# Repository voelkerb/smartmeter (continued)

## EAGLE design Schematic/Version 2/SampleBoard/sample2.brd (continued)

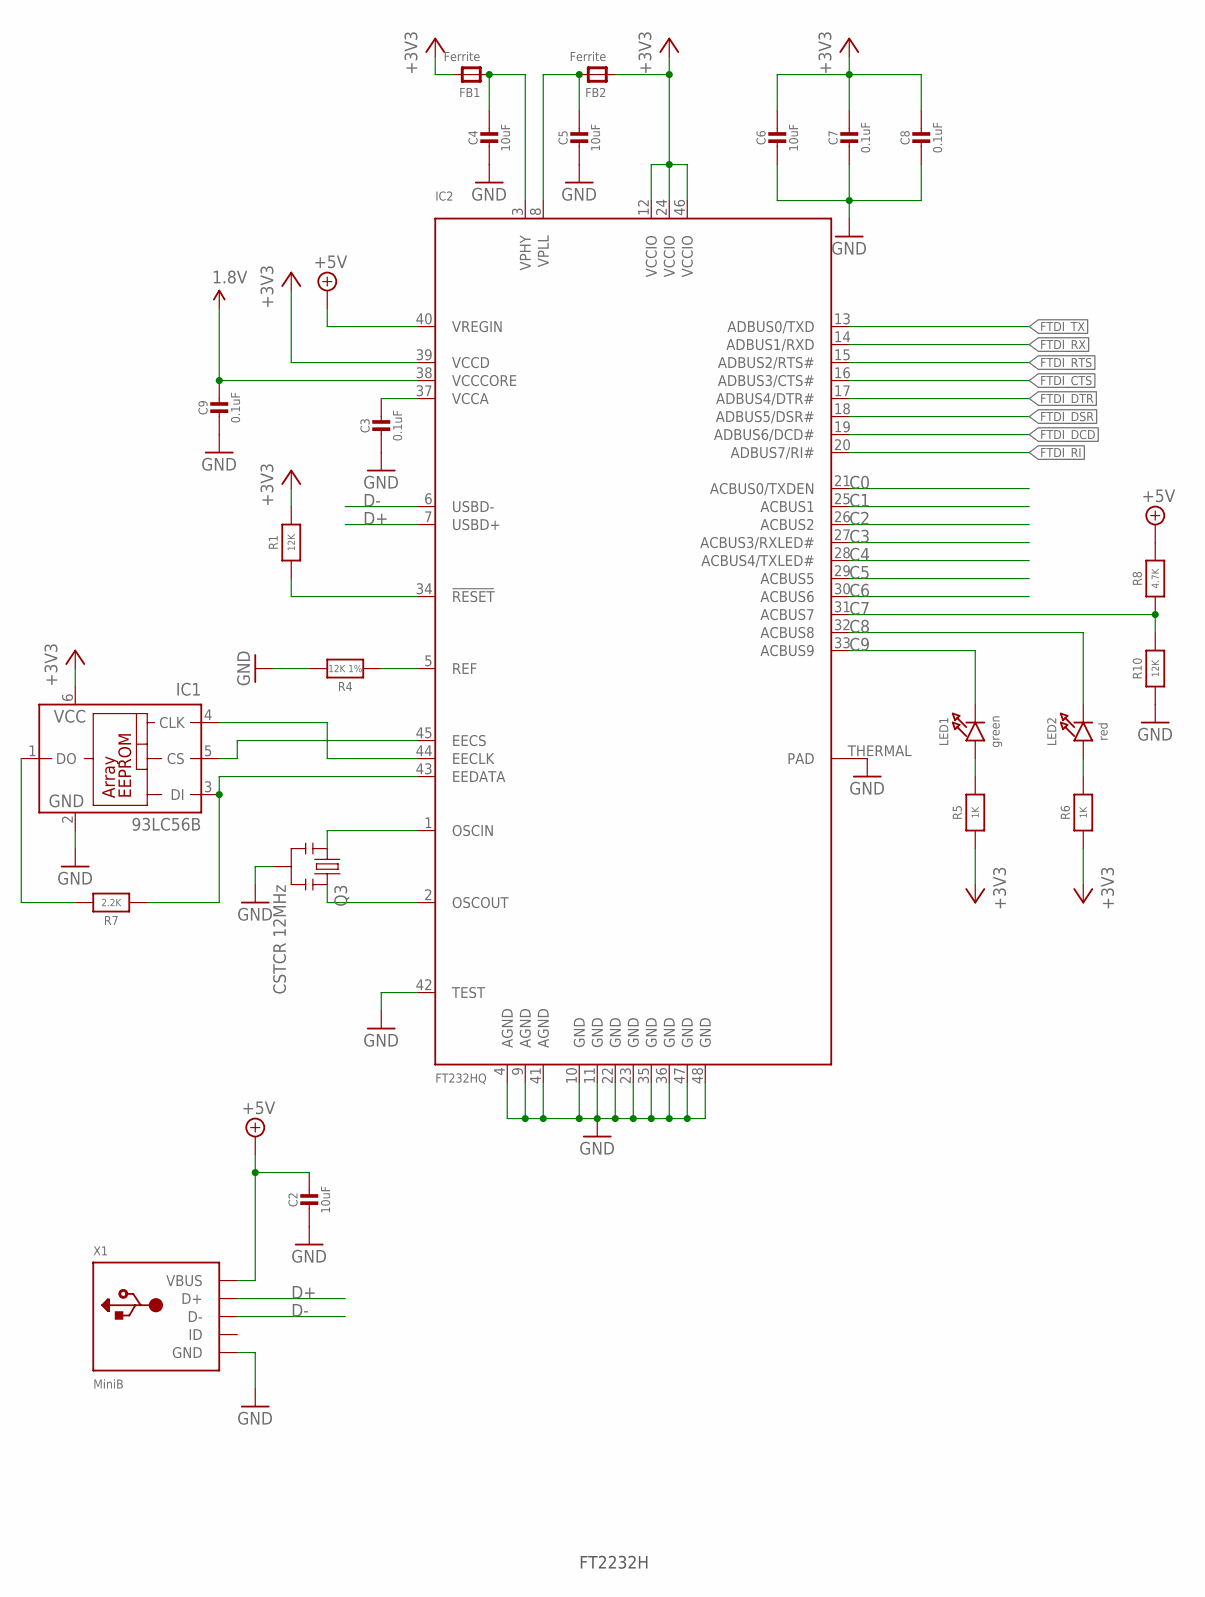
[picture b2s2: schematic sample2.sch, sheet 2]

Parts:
C2, C4, C5, C6: 10uF; _0603MP
C3, C7, C8, C9: 0.1uF; _0603MP
FB1: Ferrite; _0603
FB2: Ferrite; _0603MP
IC1: 93LC56B; SOT23-6
IC2: FT232HQ; QFN48_8MM
LED1: green; CHIPLED_0603_NOOUTLINE
LED2: red; CHIPLED_0603_NOOUTLINE
Q3: CSTCR 12MHz; RESONATOR-SMD
R1, R10: 12K; _0603MP
R4: 12K 1%; _0603MP
R5, R6: 1K; _0603MP
R7: 2.2K; _0603MP
R8: 4.7K; _0603MP
X1: MiniB; 4UCONN_20329

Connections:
1.8V: C9.1, IC2.38 (VCCCORE)
+3V3: C6.1, C7.1, C8.1, FB1.2, FB2.1, IC1.6 (VCC), IC2.12 (VCCIO), IC2.24 (VCCIO), IC2.39 (VCCD), IC2.46 (VCCIO), R1.2, R5.1, R6.1; also elsewhere on the board
+5V: C2.1, IC2.40 (VREGIN), R8.2, X1.VBUS
C0: IC2.21 (ACBUS0/TXDEN)
C1: IC2.25 (ACBUS1)
C2: IC2.26 (ACBUS2)
C3: IC2.27 (ACBUS3/RXLED#)
C4: IC2.28 (ACBUS4/TXLED#)
C5: IC2.29 (ACBUS5)
C6: IC2.30 (ACBUS6)
C7: IC2.31 (ACBUS7), R8.1, R10.2
C8: IC2.32 (ACBUS8), LED2.C
C9: IC2.33 (ACBUS9), LED1.C
D+: IC2.7 (USBD+), X1.D+
D-: IC2.6 (USBD-), X1.D-
FTDI_CTS: IC2.16 (ADBUS3/CTS#)
FTDI_DCD: IC2.19 (ADBUS6/DCD#)
FTDI_DSR: IC2.18 (ADBUS5/DSR#)
FTDI_DTR: IC2.17 (ADBUS4/DTR#); also elsewhere on the board
FTDI_RI: IC2.20 (ADBUS7/RI#)
FTDI_RTS: IC2.15 (ADBUS2/RTS#); also elsewhere on the board
FTDI_RX: IC2.14 (ADBUS1/RXD); also elsewhere on the board
FTDI_TX: IC2.13 (ADBUS0/TXD); also elsewhere on the board
GND: C2.2, C3.2, C4.2, C5.2, C6.2, C7.2, C8.2, C9.2, IC1.2 (GND), IC2.4 (AGND), IC2.9 (AGND), IC2.10 (GND), IC2.11 (GND), IC2.22 (GND), IC2.23 (GND), IC2.35 (GND), IC2.36 (GND), IC2.41 (AGND), IC2.42 (TEST), IC2.47 (GND), IC2.48 (GND), IC2.THERMAL (PAD), Q3.2, R4.2, R10.1, X1.BASE@1 (GND), X1.BASE@2 (GND), X1.GND, X1.SPRT@1 (GND), X1.SPRT@2 (GND), X1.SPRT@3 (GND), X1.SPRT@4 (GND); also elsewhere on the board
unnamed: IC2.1 (OSCIN), Q3.1
unnamed: IC2.2 (OSCOUT), Q3.3
unnamed: IC2.5 (REF), R4.1
unnamed: LED2.A, R6.2
unnamed: IC2.34 (!RESET), R1.1
unnamed: LED1.A, R5.2
unnamed: IC1.3 (DI), IC2.43 (EEDATA), R7.1
unnamed: IC1.5 (CS), IC2.45 (EECS)
unnamed: IC1.4 (CLK), IC2.44 (EECLK)
unnamed: IC1.1 (DO), R7.2
VCCA: C3.1, IC2.37 (VCCA)
VPHY: C4.1, FB1.1, IC2.3 (VPHY)
VPLL: C5.1, FB2.2, IC2.8 (VPLL)

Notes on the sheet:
FT2232H

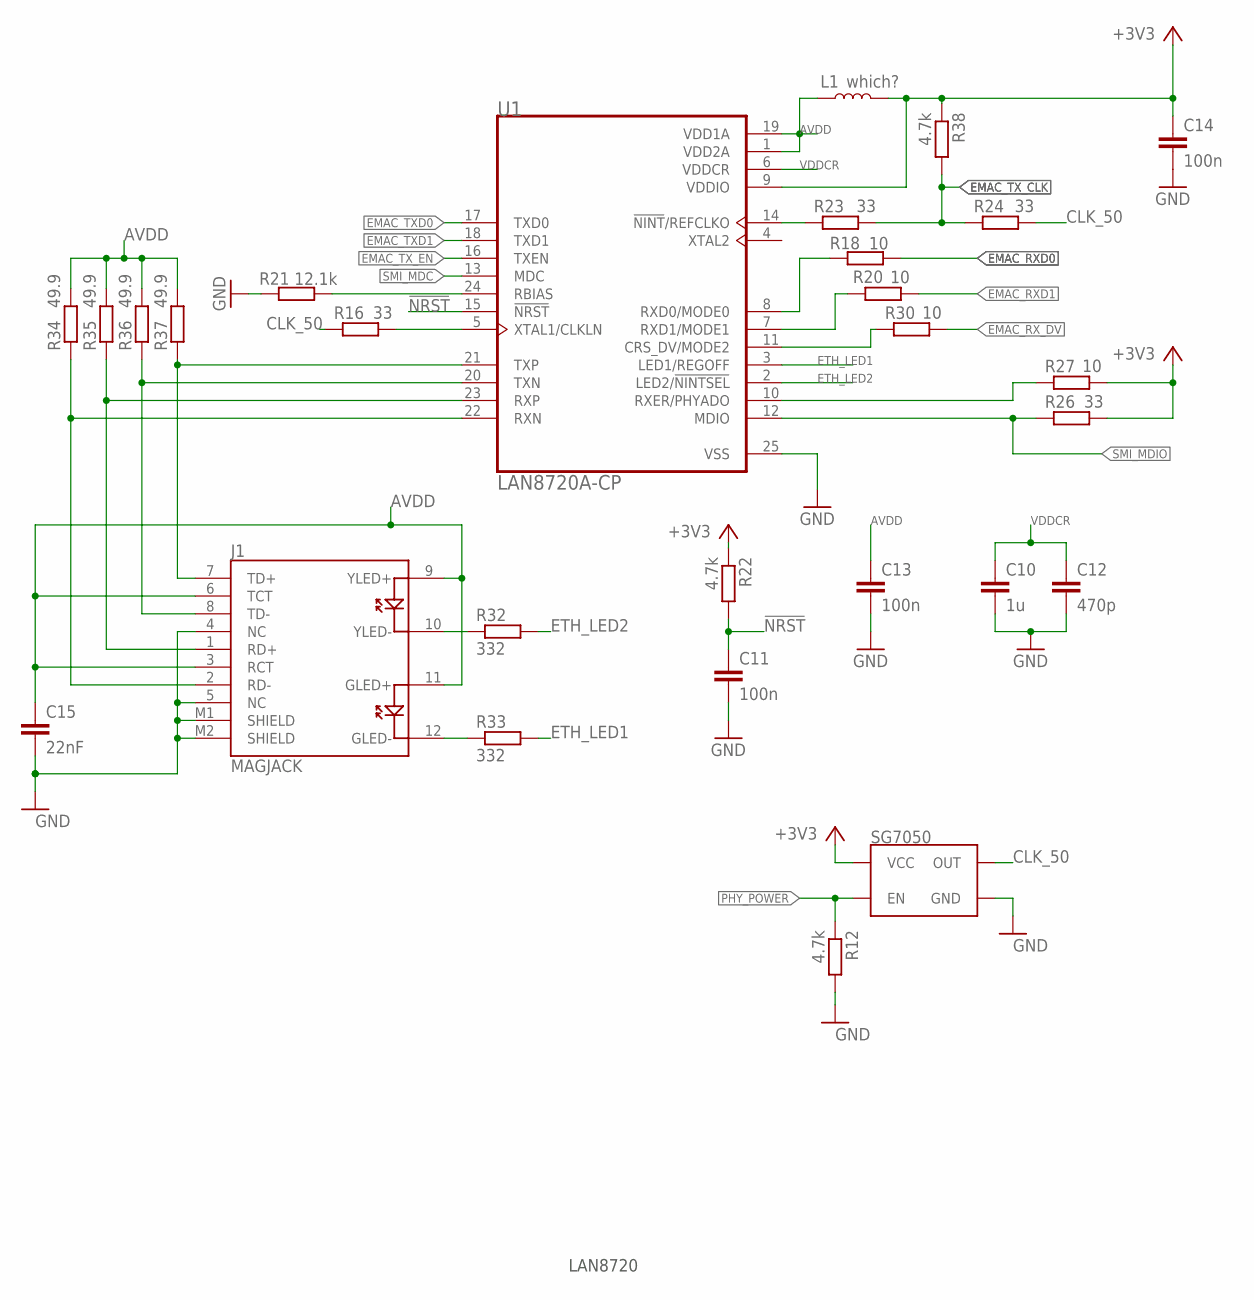
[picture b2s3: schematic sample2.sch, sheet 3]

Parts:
C10: 1u; C0402
C11, C13, C14: 100n; C0402
C12: 470p; C0402
C15: 22nF; C0402
J1: MAGJACK
L1: which?; 0603
R12, R22, R38: 4.7k; R0603
R16, R23, R24, R26: 33; R0603
R18, R20, R27, R30: 10; R0603
R21: 12.1k; R0603
R32, R33: 332; R0603
R34, R35, R36, R37: 49.9; R0603
SG7050: OSCILLATORSMD-7X5-4PAD; OSCILLATOR-SMD-7X5-4PAD
U1: LAN8720A-CP; QFN50P400X400X100-25N

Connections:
!NRST: C11.1, R22.2, U1.15 (!NRST)
+3V3: C14.1, L1.2, R22.1, R26.2, R27.2, R38.1, SG7050.4 (VCC), U1.9 (VDDIO); also elsewhere on the board
AVDD: C13.1, C15.1, J1.3 (RCT), J1.6 (TCT), J1.9 (YLED+), J1.11 (GLED+), L1.1, R34.2, R35.2, R36.2, R37.2, U1.1 (VDD2A), U1.19 (VDD1A)
CLK_50: R16.1, R24.2, SG7050.3 (OUT)
EMAC_RXD0: R18.1; also elsewhere on the board
EMAC_RXD1: R20.1; also elsewhere on the board
EMAC_RX_DV: R30.2; also elsewhere on the board
EMAC_TXD0: U1.17 (TXD0); also elsewhere on the board
EMAC_TXD1: U1.18 (TXD1); also elsewhere on the board
EMAC_TX_CLK: R23.2, R24.1, R38.2; also elsewhere on the board
EMAC_TX_EN: U1.16 (TXEN); also elsewhere on the board
ETH_LED1: R33.2, U1.3 (LED1/REGOFF)
ETH_LED2: R32.2, U1.2 (LED2/!NINTSEL!)
GND: C10.2, C11.2, C12.2, C13.2, C14.2, C15.2, J1.4 (NC), J1.5 (NC), J1.M1 (SHIELD), J1.M2 (SHIELD), R12.2, R21.2, SG7050.2 (GND), U1.25 (VSS); also elsewhere on the board
unnamed: R20.2, U1.7 (RXD1/MODE1)
unnamed: R18.2, U1.8 (RXD0/MODE0)
unnamed: R21.1, U1.24 (RBIAS)
unnamed: J1.10 (YLED-), R32.1
unnamed: R16.2, U1.5 (XTAL1/CLKLN)
unnamed: R27.1, U1.10 (RXER/PHYADO)
unnamed: R23.1, U1.14 (!NINT!/REFCLKO)
unnamed: R30.1, U1.11 (CRS_DV/MODE2)
unnamed: J1.12 (GLED-), R33.1
unnamed: J1.7 (TD+), R37.1, U1.21 (TXP)
unnamed: J1.8 (TD-), R36.1, U1.20 (TXN)
unnamed: J1.1 (RD+), R35.1, U1.23 (RXP)
unnamed: J1.2 (RD-), R34.1, U1.22 (RXN)
PHY_POWER: R12.1, SG7050.1 (EN); also elsewhere on the board
SMI_MDC: U1.13 (MDC); also elsewhere on the board
SMI_MDIO: R26.1, U1.12 (MDIO); also elsewhere on the board
VDDCR: C10.1, C12.1, U1.6 (VDDCR)

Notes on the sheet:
LAN8720

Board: 2 copper layers, 83 parts (0 on the bottom side), 79 nets, no tracks yet.

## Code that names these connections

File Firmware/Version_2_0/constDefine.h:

// Serial Speed and DEBUG option
// #define SERIAL_SPEED 115200
#define SERIAL_SPEED 2000000
// #define SERIAL_SPEED 3000000
// #define DEBUG_DEEP
#define SENT_LIFENESS_TO_CLIENTS


#define VERSION "2.0"

#define SEND_INFO_ON_CLIENT_CONNECT

// Only allow cmds over serial if we are not sampling over tcp
// #define CMD_OVER_SERIAL_WHILE_TCP_SAMPLING

// Default values
#define STANDARD_UDP_PORT 54323
#define STANDARD_TCP_SAMPLE_PORT 54321
#define STANDARD_TCP_STREAM_PORT 54322
#define DEFAULT_SR 8000


// Location time difference between us (Freiburg, Germany) and NTP time
#define LOCATION_TIME_OFFSET 3600//7200 // 2 hours or (2*60*60)

#define MDNS_UPDATE_INTERVAL 30000
#define TCP_UPDATE_INTERVAL 100
#define LIFENESS_UPDATE_INTERVAL 1000
#define RTC_UPDATE_INTERVAL 30000
#define STREAM_SERVER_UPDATE_INTERVAL 30000
#define MQTT_UPDATE_INTERVAL 5000

// We allow a max of 3 tcp clients for performance reasons
#define MAX_CLIENTS 3

const char * LOG_FILE = "/log.txt";

const char LOG_PREFIX_SERIAL[] = "Info:";
const char LOG_PREFIX[] = "Info:";

const char DATA_PREFIX[] = "Data:";
const size_t PREFIX_SIZE = strlen(DATA_PREFIX); 


// All available pins of ESP32
#define IO0 0
#define IO1 1 // UART 0 TX
#define IO2 2
#define IO3 3 // UART 0 RX
#define IO4 4 // HSPI H0
#define IO5 5 // Strapping (must be pulled low at boot)
#define IO6 6 // SPI CLK      // Blocked for SPI Flash
#define IO7 7 // SPI Q        // Blocked for SPI Flash
#define IO8 8 // SPI          // Blocked for SPI Flash
#define IO9 9 // UART 1 RX    // Blocked for SPI Flash
#define IO10 10 // UART 1 TX  // Blocked for SPI Flash
#define IO11 11 // SPI CS     // Blocked for SPI Flash
#define IO12 12 // HSPI Q     // Strapping (must be pulled low at boot)
#define IO13 13 // HSPI ID
#define IO14 14 // HSPI CLK   // Strapping
#define IO15 15 // HSPI CS    // Strapping
#define IO16 16 // Not Available (PSRAM)
#define IO17 17 // Not Available (PSRAM)
#define IO18 18 // VSPI CLK
#define IO19 19 // VSPI MOSI
// #define IO20 20 // non existent
#define IO21 21 // VSPI H2
#define IO22 22 // VSPI WP
#define IO23 23 // VSPI MISO
// #define IO24 24 // non existent
#define IO25 25 // DAC_1
#define IO26 26 // DAC_2
#define IO27 27
// #define IO28 28 // non existent
// #define IO29 29 // non existent
// #define IO30 30 // non existent
// #define IO31 31 // non existent
#define IO32 32
#define IO33 33
#define IO34 34  // Input only
#define IO35 35  // Input only
#define IO36 36  // Input only
// #define IO37 37 // non existent
// #define IO38 38 // non existent
#define IO39 39  // Input only



// ADE Things
#define ADE_SPI_BUS VSPI
// // TODO: Change
#define ADE_RESET_PIN   IO2
// NOTE: Sharing the same pin as ERROR LED; Obacht  
#define ADE_PM1_PIN   IO4
// // Event Pin/Data Ready
#define ADE_DREADY_PIN    IO34


// Used SPI pins
// TODO: Does this work?
#define ADE_SCK IO12
#define ADE_MISO IO13
#define ADE_CS IO14
#define ADE_MOSI IO15


// Ethernet RMII
#define PHY_POWER   IO5
#define EMAC_TX_EN  IO21
#define EMAC_TXD0   IO19
#define EMAC_TXD1   IO22
#define EMAC_RXD0   IO25
#define EMAC_RXD1   IO26
#define EMAC_RX_DV  IO27
#define EMAC_TX_CLK IO0
#define SMI_MDC     IO23
#define SMI_MDIO    IO18

// RTC
#define SDA     IO32
#define SCL     IO33
#define RTC_INT IO36



#define ERROR_LED IO4

// AVAILABLE Pins
// IO1  // UART TX
// IO3  // UART RX
// IO4

// IDEA:
// ADE:
// N_IRQ0_PIN  IO36 // input
// N_IRQ1_PIN  IO39 // input
// Über iO expander:
// PM0_PIN      // output
// PM1_PIN      // output
// CF1          // output
// CF2          // output
// CF3          // output
// CF4          // output


// Buffering stuff
#define MAX_SEND_SIZE 1024 // 512
// PSRAM Buffer
const int PS_BUF_SIZE = 3*1024*1024 + 512*1024;
const int RAM_BUF_SIZE = 40*1024;
#define COMMAND_MAX_SIZE 400

// Communication commands
#define CMD_SAMPLE "sample"
#define CMD_REQ_SAMPLES "reqSamples"
#define CMD_FLOW "cts"
#define CMD_STOP "stop"
#define CMD_RESTART "restart"
#define CMD_FACTORY_RESET "factoryReset"
#define CMD_BASIC_RESET "basicReset"
#define CMD_INFO "info"
#define CMD_MDNS "mdns"
#define CMD_NTP "ntp"
#define CMD_ADD_WIFI "addWifi"
#define CMD_REMOVE_WIFI "delWifi"
#define CMD_CLEAR_LOG "clearLog"
#define CMD_GET_LOG "getLog"
#define CMD_MQTT_SERVER "mqttServer"
#define CMD_STREAM_SERVER "streamServer"
#define CMD_TIME_SERVER "timeServer"
#define CMD_LOG_LEVEL "log"

#define LOG_LEVEL_ALL "all"
#define LOG_LEVEL_DEBUG "debug"
#define LOG_LEVEL_INFO "info"
#define LOG_LEVEL_WARNING "warning"
#define LOG_LEVEL_ERROR "error"

#define MAX_UNIT_STR_LENGTH 20
#define MAX_MEASURE_STR_LENGTH 20

#define MEASURE_VI "v,i,v,i,v,i"
#define MEASURE_VI_COMPATIBILITY "v,i"
#define MEASURE_VI_L1 "v,i_L1"
#define MEASURE_VI_L2 "v,i_L2"
#define MEASURE_VI_L3 "v,i_L3"
#define MEASURE_PQ "p,q"
#define MEASURE_PQ_LONG "p,p,p,q,q,q"
#define MEASURE_VI_RMS "v,i_RMS"
#define MEASURE_VI_RMS_LONG "v,v,v,i,i,i_RMS"


#define UNIT_VI "V,mA,V,mA,V,mA"
#define UNIT_VI_LX "V,mA"
#define UNIT_PQ "W,W,W,VAR,VAR,VAR"
#define UNIT_VI_RMS "V,V,V,mA,mA,mA"

#include <ETH.h>
#define ETH_CLK_MODE    ETH_CLOCK_GPIO0_IN//ETH_CLOCK_GPIO17_OUT//ETH_CLOCK_GPIO0_IN//ETH_CLOCK_GPIO17_OUT
// Pin# of the enable signal for the external crystal oscillator (-1 to disable for internal APLL source)
#define ETH_POWER_PIN   PHY_POWER
// Type of the Ethernet PHY (LAN8720 or TLK110)
#define ETH_TYPE        ETH_PHY_LAN8720
// I²C-address of Ethernet PHY (0 or 1 for LAN8720, 31 for TLK110)
#define ETH_ADDR        1
// Pin# of the I²C clock signal for the Ethernet PHY
#define ETH_MDC_PIN     SMI_MDC
// Pin# of the I²C IO signal for the Ethernet PHY
#define ETH_MDIO_PIN    SMI_MDIO



#define MAX_STRING_LENGTH_STACK 40


#define MQTT_TOPIC_BASE "powermeter"
#define MQTT_TOPIC_SEPARATOR '/'
#define MQTT_TOPIC_SWITCH "switch"
#define MQTT_TOPIC_SWITCH_ON "on"
#define MQTT_TOPIC_SWITCH_OFF "off"
#define MQTT_TOPIC_SAMPLE "sample"
#define MQTT_TOPIC_SAMPLING "sampling"
#define MQTT_TOPIC_STATE "state"
#define MQTT_TOPIC_CMD "cmd"
#define MQTT_TOPIC_INFO "info"

#define MAX_MQTT_TOPIC_LEN MAX_MQTT_PUB_TOPIC_SWITCH+MAX_NAME_LEN

const int MAX_MQTT_PUB_TOPIC_SWITCH = sizeof(MQTT_TOPIC_BASE) + sizeof(MQTT_TOPIC_STATE) + sizeof(MQTT_TOPIC_SWITCH) + 4*sizeof(MQTT_TOPIC_SEPARATOR) + 2;
const int MAX_MQTT_PUB_TOPIC_SAMPLE = sizeof(MQTT_TOPIC_BASE) + sizeof(MQTT_TOPIC_STATE) + sizeof(MQTT_TOPIC_SAMPLE) + 4*sizeof(MQTT_TOPIC_SEPARATOR) + 2;
const int MAX_MQTT_PUB_TOPIC_INFO = sizeof(MQTT_TOPIC_BASE) + sizeof(MQTT_TOPIC_STATE) + sizeof(MQTT_TOPIC_INFO) + 4*sizeof(MQTT_TOPIC_SEPARATOR) + 2;



template < typename TOut, typename TIn >
TOut round2( TIn value ) {
   return static_cast<TOut>((int)(value * 100 + 0.5) / 100.0);
}

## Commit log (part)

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2018-11-07 initial commit of current working ino file
2018-11-07 Added UDP ready Version
2018-11-07 changed makefile such that project can be build right away
2018-11-07 Added files
2019-09-06 Added Versioning and fixed \r\n buf
2019-11-12 added submodules
2019-11-12 added version 2.0
2019-11-22 Subrepos added, Firmware Version 2.0 basicly running
    - Repos from smartenergy.powermeter (e.g. rinngbuffer,rtc,etc.) finally embedded into smartmeter as subrepos
    - Subrepos must be placed and cloned into each Firmware version separately in <ino Folder>/src/<subrepo name> (use git submodule add http://foo.git bar/)
    - Version 2.0 is basically running with ADE9000:
    -- will not work with old Board HW (#define pins of ADE have changed)
    -- keeping samplingrate is a bit hacky and will only work if external ADE CLK is faster than RTC
    -- samplerates can only be chosen as /2 devider of 32 kHz (16k,8k,4k,2k,1k,1.6k,0.8k,0.5k,0.4k,0.2k,0.1k)
2019-12-02 Fixed sampling causing reset after second sampling attempt
2019-12-02 updated submodules
2020-01-20 added solidworks 3D parts of housing and nc files
2020-01-20 Added kernel extension for 12Mbaud speed with FTDI
2020-01-21 added multiclient support for tcp connections
2020-02-05 Added MQTT to V2, added working version 1_1, added arduino pluugins
2020-02-06 added parse command ino fie
2020-02-11 fiexed MQTT bug and added ade9000 rms and power reading
2020-02-12 added datasheet of ade9000, added arduino files from analog devices
2020-02-19 added MQTT sampling together with latched smapling, allowing to get P,Q as well. Closing Ticket #442
2020-02-19 minor improvements
2020-02-19 added streamserver functionality, closing feature #438
2020-02-19 hotfix, OTA not working due to streamserver connect
2020-02-20 fixed issue #453 -> null on mqtt sampling and #454 -> stop command
2020-03-09 minor bugfix
2020-03-12 Closing #459 parallel ntp sync
2020-03-12 Added PowerMeterV2 to Arduino Boards txt
2020-03-17 Added MQTT for homebridge worked on #460. Still not closed 100%
2020-03-17 addWifi Command now returns if wifi alread in list
2020-03-19 fixed #462 and some mqtt stuff
2020-04-28 working on #477 and #481 #478
2020-05-12 Fixing bug #485 hopefully, at least working on it..
2020-05-12 deleted vsc stuff
2020-05-15 added esptool
2020-05-18 added possibility to force updatge ntp in background
2021-03-08 cleanup
2021-03-08 more docu
2021-03-08 reference to powermeter
2021-03-08 compile info
2021-03-08 changed to new unified ESP32 ESP8266 libraries
2021-03-08 relative include for arduino
2021-03-08 added installation picture
2021-03-08 small docu fix
2021-03-08 added docu
2021-08-12 include energy
2021-08-12 include compile time constant explanation
2021-08-12 added energy, calibration, and reset command
2021-08-12 Support for energy
2021-08-12 gitmodules merge now
2021-09-21 added privateConf
2021-09-21 added docu for resetEnergy+get elctrical measurements
2021-09-21 store energy startTs
2021-09-21 phaseAngle and period
2021-09-21 removed constants, privateConf, energy commands
2021-09-21 energy commands, rewritten command handler
2021-11-03 newest revision
2021-11-03 fixed measurement jitter by reverting to ISR used for FIRED
